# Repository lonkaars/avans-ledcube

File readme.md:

# avans-ledcube

(in dutch again haha)

onze ledcube is iets anders dan de gemiddelde ledcube. onze leds zijn
aangesloten als een 8x8 matrix waarbij alle anodes in rijen, en alle cathodes
in kolommen zijn verbonden. hierdoor gebruikt onze ledcube maar acht
weerstanden inplaats van zestien, en geen transistoren of mosfets. ook worden
maar drie uitgangen van de arduino gebruikt voor de seriële ingang, seriële
klok, en de latch klok van het shiftregister.

## coole functies

- algoritme om lege scanrijen over te slaan voor een hogere felheid
- instelbare lengte en volgorde van de effecten die afspelen
- makkelijk uitbereidbaar met nieuwe effecten
- goed gedocumenteerd
- opgesplitst in losse bestanden voor overzichtelijkheid
- ingebouwde led map zodat je coordinaten kunt gebruiken in je animatiecode
- veganistisch vriendelijk

## software

de software is als gevolg van de ongewone aansluitingswijze ook anders
ingericht. de atmega328p heeft ingebouwde pwm timers, die je zou kunnen
gebruiken om snel door de vier lagen van de ledcube heen te schakelen. omdat
deze timers los van je code draaien kun je de ingebouwde `delay()` gewoon
gebruiken om de animaties makkelijker te implementeren, maar dit werkt alleen
wanneer je transistoren gebruikt en ze direct op pwm uitgangen aansluit.

daarom gebruikt onze software geen `delay()` of andere 'blokkerende' functies,
maar timers. dit zorgt ervoor dat de ingebouwde `loop()` functie van de arduino
vaak genoeg draait om het te laten lijken alsof alle led's van de ledcube
tegelijkertijd aan zijn.

de software is opgesplitst in losse bestanden om overzichtelijkheid te
behouden. alle documentatie bevindt zich in de header (.h) bestanden, is in het
engels, en is in doxygen formaat. hier is een beknopte beschrijving van de
bestanden:

```
software/
├── animation.h      --
├── animation.ino    helpfuncties voor animaties
├── consts.h         algemene constantes
├── effects.h        bevat ook opties voor de diavoorstelling van animaties
├── effects.ino      de animaties die weergeven worden
├── readme.md        dit bestand
├── scan.h           --
├── scan.ino         functies omtrent het schakelen van de rijen
├── shift.h          --
├── shift.ino        functies die het shiftregister besturen
├── software.h       --
├── software.ino     hoofdbestand/ingangspunt
├── util.h           --
└── util.ino         gereedschapsfuncties
```

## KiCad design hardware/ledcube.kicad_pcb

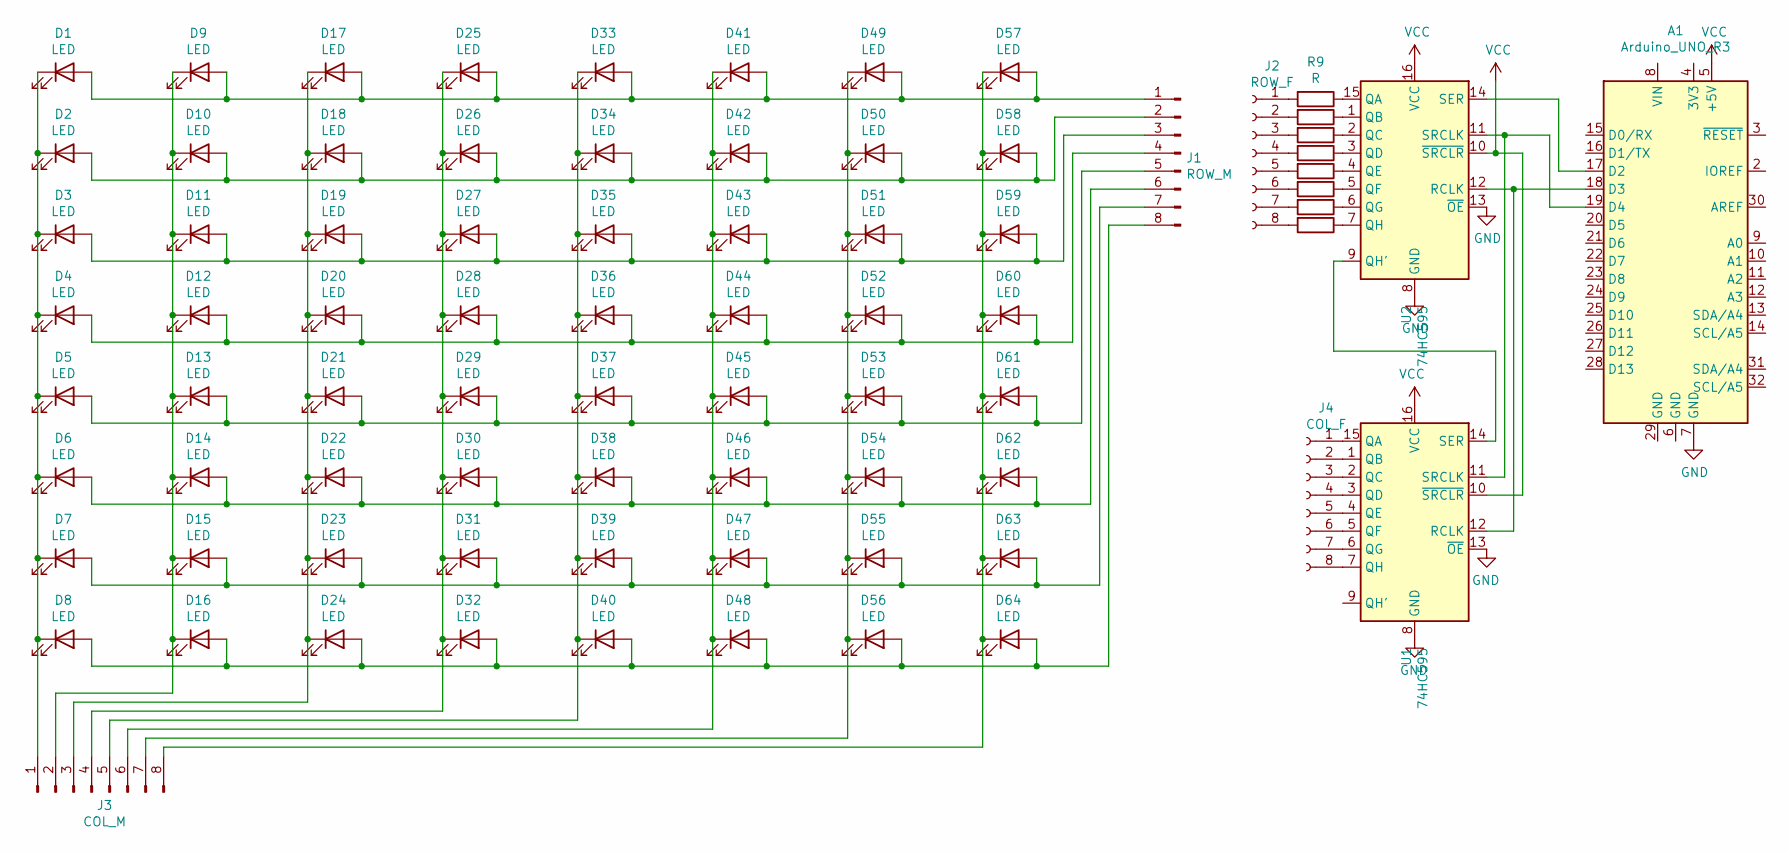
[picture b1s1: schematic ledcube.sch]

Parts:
A1: Arduino_UNO_R3
D1, D2, D3, D4, D5, D6, D7, D8, D9, D10, D11, D12, D13, D14, D15, D16, D17, D18, D19, D20, D21, D22, D23, D24, D25, D26, D27, D28, D29, D30, D31, D32, D33, D34, D35, D36, D37, D38, D39, D40, D41, D42, D43, D44, D45, D46, D47, D48, D49, D50, D51, D52, D53, D54, D55, D56, D57, D58, D59, D60, D61, D62, D63, D64: LED; LED_D3.0mm
J1: ROW_M; PinSocket_1x08_P2.54mm_Vertical
J2: ROW_F; PinHeader_1x08_P2.54mm_Vertical
J3: COL_M; PinSocket_1x08_P2.54mm_Vertical
J4: COL_F; PinHeader_1x08_P2.54mm_Vertical
R9, R10, R11, R12, R13, R14, R15, R16: R; R_Axial_DIN0207_L6.3mm_D2.5mm_P10.16mm_Horizontal
U1, U2: 74HC595

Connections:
GND: A1.7 (GND), U1.8 (GND), U1.13 (~OE), U2.8 (GND), U2.13 (~OE)
unnamed: A1.17 (D2), U2.14 (SER)
unnamed: A1.18 (D3), U1.12 (RCLK), U2.12 (RCLK)
unnamed: A1.19 (D4), U1.11 (SRCLK), U2.11 (SRCLK)
unnamed: D1.1 (K), D2.1 (K), D3.1 (K), D4.1 (K), D5.1 (K), D6.1 (K), D7.1 (K), D8.1 (K), J3.1
unnamed: D1.2 (A), D9.2 (A), D17.2 (A), D25.2 (A), D33.2 (A), D41.2 (A), D49.2 (A), D57.2 (A), J1.1
unnamed: D9.1 (K), D10.1 (K), D11.1 (K), D12.1 (K), D13.1 (K), D14.1 (K), D15.1 (K), D16.1 (K), J3.2
unnamed: D2.2 (A), D10.2 (A), D18.2 (A), D26.2 (A), D34.2 (A), D42.2 (A), D50.2 (A), D58.2 (A), J1.2
unnamed: D3.2 (A), D11.2 (A), D19.2 (A), D27.2 (A), D35.2 (A), D43.2 (A), D51.2 (A), D59.2 (A), J1.3
unnamed: D4.2 (A), D12.2 (A), D20.2 (A), D28.2 (A), D36.2 (A), D44.2 (A), D52.2 (A), D60.2 (A), J1.4
unnamed: D5.2 (A), D13.2 (A), D21.2 (A), D29.2 (A), D37.2 (A), D45.2 (A), D53.2 (A), D61.2 (A), J1.5
unnamed: D6.2 (A), D14.2 (A), D22.2 (A), D30.2 (A), D38.2 (A), D46.2 (A), D54.2 (A), D62.2 (A), J1.6
unnamed: D7.2 (A), D15.2 (A), D23.2 (A), D31.2 (A), D39.2 (A), D47.2 (A), D55.2 (A), D63.2 (A), J1.7
unnamed: D8.2 (A), D16.2 (A), D24.2 (A), D32.2 (A), D40.2 (A), D48.2 (A), D56.2 (A), D64.2 (A), J1.8
unnamed: D17.1 (K), D18.1 (K), D19.1 (K), D20.1 (K), D21.1 (K), D22.1 (K), D23.1 (K), D24.1 (K), J3.3
unnamed: D25.1 (K), D26.1 (K), D27.1 (K), D28.1 (K), D29.1 (K), D30.1 (K), D31.1 (K), D32.1 (K), J3.4
unnamed: D33.1 (K), D34.1 (K), D35.1 (K), D36.1 (K), D37.1 (K), D38.1 (K), D39.1 (K), D40.1 (K), J3.5
unnamed: D41.1 (K), D42.1 (K), D43.1 (K), D44.1 (K), D45.1 (K), D46.1 (K), D47.1 (K), D48.1 (K), J3.6
unnamed: D49.1 (K), D50.1 (K), D51.1 (K), D52.1 (K), D53.1 (K), D54.1 (K), D55.1 (K), D56.1 (K), J3.7
unnamed: D57.1 (K), D58.1 (K), D59.1 (K), D60.1 (K), D61.1 (K), D62.1 (K), D63.1 (K), D64.1 (K), J3.8
unnamed: J2.1, R9.2
unnamed: J2.2, R10.2
unnamed: J2.3, R11.2
unnamed: J2.4, R12.2
unnamed: J2.5, R13.2
unnamed: J2.6, R14.2
unnamed: J2.7, R15.2
unnamed: J2.8, R16.2
unnamed: J4.1, U1.15 (QA)
unnamed: J4.2, U1.1 (QB)
unnamed: J4.3, U1.2 (QC)
unnamed: J4.4, U1.3 (QD)
unnamed: J4.5, U1.4 (QE)
unnamed: J4.6, U1.5 (QF)
unnamed: J4.7, U1.6 (QG)
unnamed: J4.8, U1.7 (QH)
unnamed: R9.1, U2.15 (QA)
unnamed: R10.1, U2.1 (QB)
unnamed: R11.1, U2.2 (QC)
unnamed: R12.1, U2.3 (QD)
unnamed: R13.1, U2.4 (QE)
unnamed: R14.1, U2.5 (QF)
unnamed: R15.1, U2.6 (QG)
unnamed: R16.1, U2.7 (QH)
unnamed: U1.14 (SER), U2.9 (QH')
VCC: A1.5 (+5V), U1.10 (~SRCLR), U1.16 (VCC), U2.10 (~SRCLR), U2.16 (VCC)

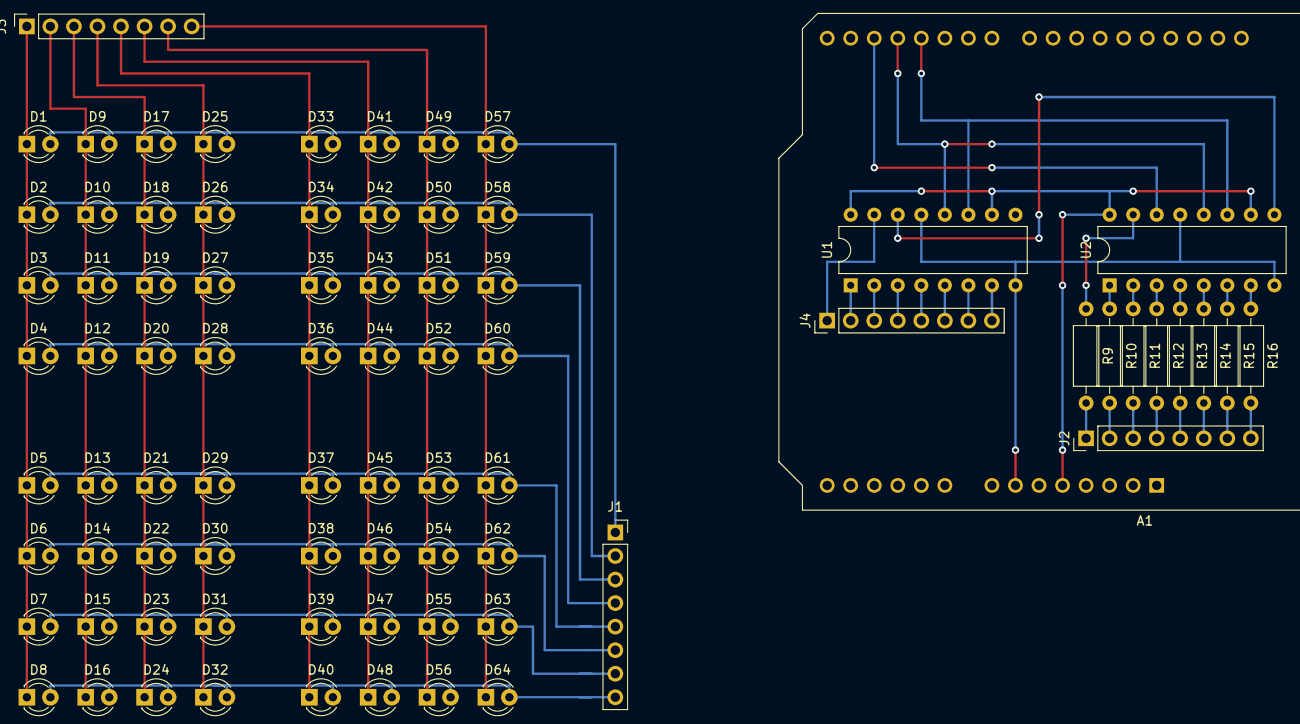
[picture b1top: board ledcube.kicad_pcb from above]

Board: 2 copper layers, 79 parts (0 on the bottom side), 46 nets.

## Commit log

2021-11-21 design document
2021-11-21 design document done
2021-11-24 software
2021-11-25 worky software
2021-11-26 working software
2021-11-26 added documentation comments and led map
2021-11-26 first animation done
    - added variable length animations
    - added readme to software subdirectory
    - implemented first animation
2021-11-26 added readme at root
2021-11-26 whoopsie in readme and moved shit into tests/ folder
2021-11-27 implemented animation 2
2021-11-27 implemented animation 3
    also fixed memory leak caused by pointer arithmetic -> 0xf0 != 0x10
2021-11-30 fix compiler warnings and ready for testing `optimize_scan()`
2021-11-30 fix animation 1 and 3 TODO: 2
2021-11-30 move and update readme's
2021-11-30 animation 2 working
2021-11-30 vertical scanning fixed
2021-11-30 fixed(?) optimize_scan, testing tomorrow...
2021-12-02 fix scan_optimize and update readme
